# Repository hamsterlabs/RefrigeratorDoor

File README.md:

# Refrigerator Door Project

Make a gadget to detect whether someone has left a door or cabinet open.

## Tools
* EagleCAD
* Arduino Studio

## Supported Development Platform

Surprise me. I am using Windows 10. No reason you could not use something else.

### C++ PhotoInterruptor Class

If the beam is broken, sample() returns true because the logic level at the top 
of the transistor is about 5 VDC.

If the beam is not broken, sample() returns false because the logic level is close to 0 VDC.

```
#include "Arduino.h"

#ifndef PhotoInterruptor_h
#define PhotoInterruptor_h

class PhotoInterruptor
{

  private:
    int sentryLED = 0;          // LED to turn on when the beam is broken
    int flash = 11;             // LED half of photointerruptor
    int IPin  =  7;             // PhotoTransistor
    bool beamBroken = false;    // true for broken beam
  
  public:
    PhotoInterruptor(int iPin, int ledPin);
    void init( int iPin, int ledPin );
    void controlLED(bool led_on);
    bool sample();
    void setSentryLED(int ledPin);
};
#endif
```

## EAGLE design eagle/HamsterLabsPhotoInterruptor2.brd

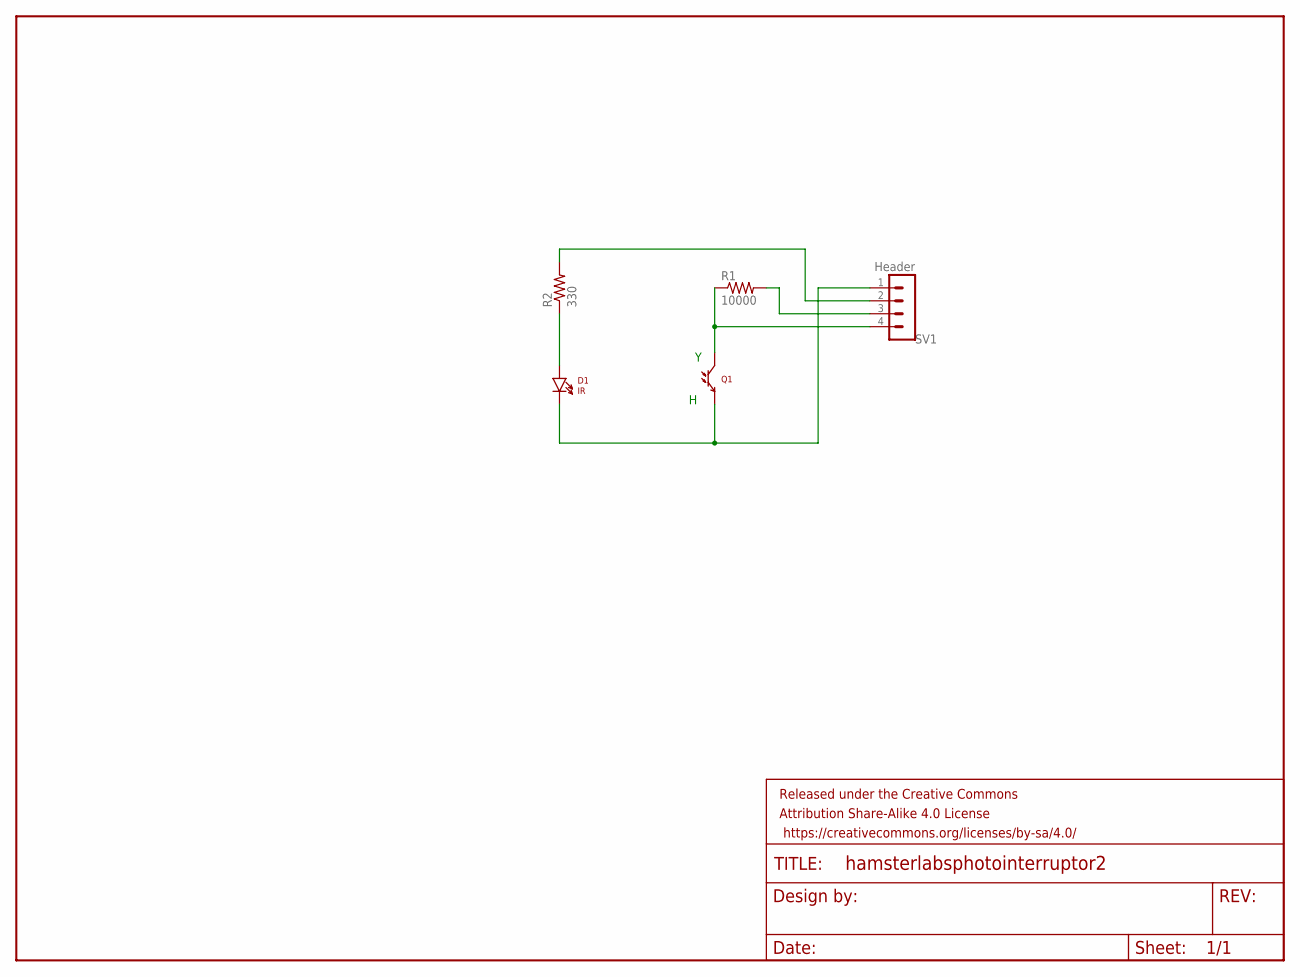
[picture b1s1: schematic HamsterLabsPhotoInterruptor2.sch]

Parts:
D1: IR; LTE-302
FRAME1: FRAME-LETTERNO_PACKAGE; DUMMY
Q1: LTR-301
R1: 10000; AXIAL-0.3
R2: 330; AXIAL-0.3
SV1: Header; MA04-1

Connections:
unnamed: D1.A, R2.P$1 (1)
unnamed: Q1.C, R1.P$1 (1), SV1.4
unnamed: R1.P$2 (2), SV1.3
unnamed: D1.C, Q1.E, SV1.1
unnamed: R2.P$2 (2), SV1.2

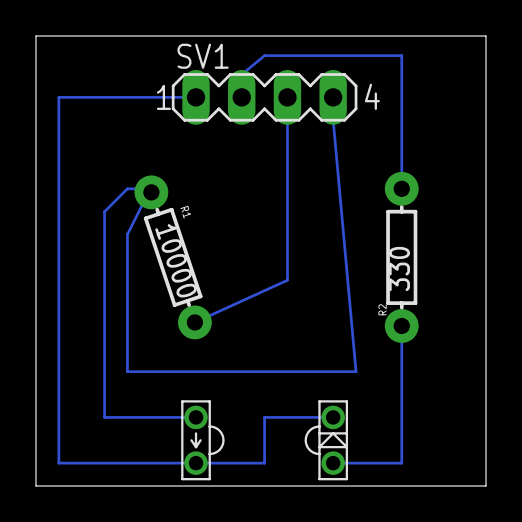
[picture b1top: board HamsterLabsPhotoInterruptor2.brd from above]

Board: 2 copper layers, 25.0 x 25.0 mm, 6 parts (0 on the bottom side), 5 nets.

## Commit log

2018-11-06 Added source code. Untested lately. might work.
2018-11-11 fixed PhotoInterruptor circuit, still testing class
2018-11-11 Circuit diagram
    Add screen shot of the photo interrupter circuit.
2018-11-11 Added to the README.md and simplified the PhotoInterruptor C++ class
2018-11-11 Updated the README
    included information about the C++ class
2018-11-11 Create LICENSE.TXT
    MIT License with additional text to include hardware.

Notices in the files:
parts and their libraries:
SparkFun-LED: Licensing: Creative Commons ShareAlike 4.0 International - https://creativecommons.org/licenses/by-sa/4.0
SparkFun-Aesthetics: Released under the Creative Commons Attribution Share-Alike 4.0 License
SparkFun-Aesthetics: https://creativecommons.org/licenses/by-sa/4.0
